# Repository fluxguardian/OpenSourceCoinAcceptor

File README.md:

# OpenSourceCoinAcceptor
 An open source coin acceptor

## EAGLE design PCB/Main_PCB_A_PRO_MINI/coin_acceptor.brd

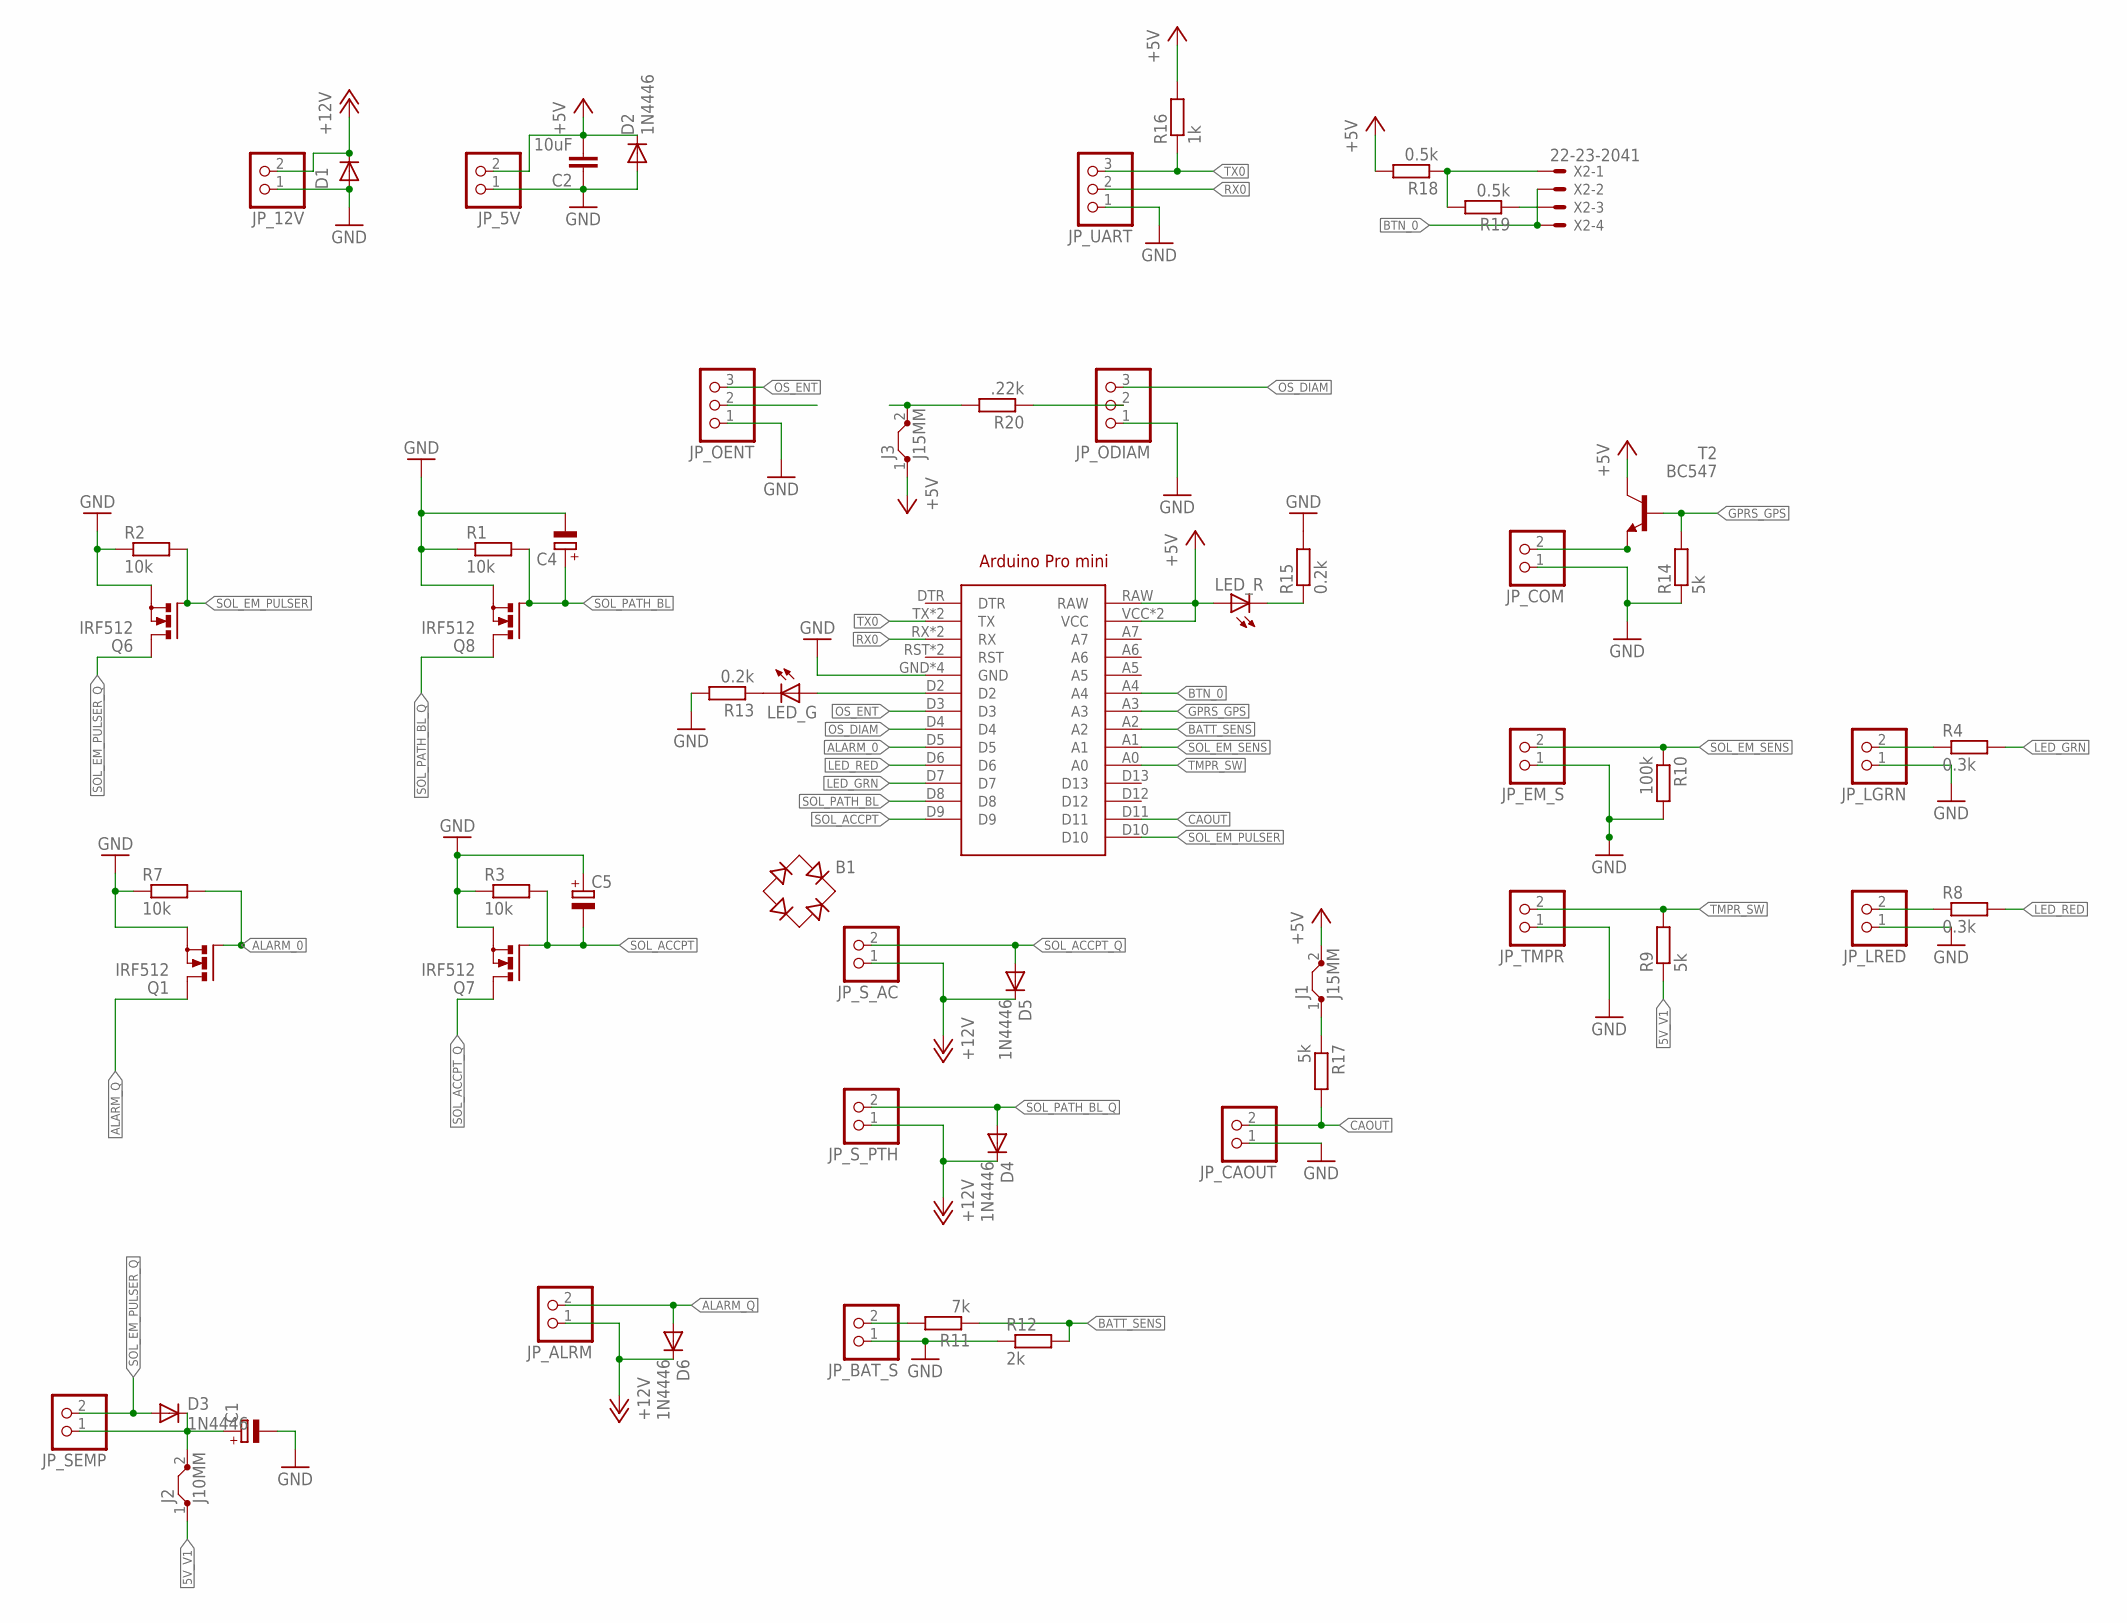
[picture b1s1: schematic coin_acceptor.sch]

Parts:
ARDUINO1: ARDUINO_PRO_MINI
B1: RB1A
C1, C4, C5: CPOL-EUE2.5-5; E2,5-5
C2: 10uF; C025-024X044
D1, D2, D3, D4, D5, D6: 1N4446; DO35-10
J1, J3: J15MM; 15
J2: J10MM; 10
JP_5V, JP_12V: PINHD-1X2; 1X02
JP_ALRM: PINHD-1X2; 1X02
JP_BAT_S: PINHD-1X2; 1X02
JP_CAOUT: PINHD-1X2; 1X02
JP_COM: PINHD-1X2; 1X02
JP_EM_S: PINHD-1X2; 1X02
JP_LGRN: PINHD-1X2; 1X02
JP_LRED: PINHD-1X2; 1X02
JP_ODIAM: PINHD-1X3; 1X03
JP_OENT: PINHD-1X3; 1X03
JP_SEMP: PINHD-1X2; 1X02
JP_S_AC: PINHD-1X2; 1X02
JP_S_PTH: PINHD-1X2; 1X02
JP_TMPR: PINHD-1X2; 1X02
JP_UART: PINHD-1X3; 1X03
LED_G: LED5MM
LED_R: LED5MM
Q1, Q6, Q7, Q8: IRF512; TO220BV
R1, R2, R3, R7: 10k; 0309/10
R4, R8: 0.3k; 0309/10
R9, R14, R17: 5k; 0309/10
R10: 100k; 0309/10
R11: 7k; 0309/10
R12: 2k; 0309/10
R13, R15: 0.2k; 0309/10
R16: 1k; 0309/10
R18, R19: 0.5k; 0309/10
R20: .22k; 0309/10
T2: BC547; TO92
X2: 22-23-2041

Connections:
5V_V0: C1.+, D3.C, J2.2, JP_SEMP.1
5V_V1: J1.1, J2.1, R9.1, R17.1
+5V: ARDUINO1.RAW, ARDUINO1.VCC, ARDUINO1.VCC@1 (VCC), C2.2, D2.C, J1.2, J3.1, JP_5V.2, LED_R.A, R16.2, R18.2, T2.3 (C)
+12V: D1.C, D4.C, D5.C, D6.C, JP_12V.2, JP_ALRM.1, JP_S_AC.1, JP_S_PTH.1
ALARM_0: ARDUINO1.D5, Q1.G, R7.2
ALARM_Q: D6.A, JP_ALRM.2, Q1.D
BATT_SENS: ARDUINO1.A2, R11.1, R12.2
BTN_0: ARDUINO1.A4, X2.2, X2.4
CAOUT: ARDUINO1.D11, JP_CAOUT.2, R17.2
COM_Q: JP_COM.2, T2.1 (E)
GND: ARDUINO1.GND, ARDUINO1.GND@1 (GND), ARDUINO1.GND@2 (GND), ARDUINO1.GND@3 (GND), C1.-, C2.1, C4.-, C5.+, D1.A, D2.A, JP_5V.1, JP_12V.1, JP_BAT_S.1, JP_CAOUT.1, JP_COM.1, JP_EM_S.1, JP_LGRN.1, JP_LRED.1, JP_ODIAM.1, JP_OENT.1, JP_TMPR.1, JP_UART.1, Q1.S, Q6.S, Q7.S, Q8.S, R1.1, R2.1, R3.1, R7.1, R10.2, R12.1, R13.2, R14.1, R15.2
GPRS_GPS: ARDUINO1.A3, R14.2, T2.2 (B)
LED_GRN: ARDUINO1.D7, R4.2
LED_RED: ARDUINO1.D6, R8.2
LGRN_Q: JP_LGRN.2, R4.1
LRED_Q: JP_LRED.2, R8.1
unnamed: JP_BAT_S.2, R11.2
unnamed: ARDUINO1.D2, LED_G.A
unnamed: LED_G.K (C), R13.1
unnamed: LED_R.K (C), R15.1
unnamed: J3.2, R20.2
unnamed: R18.1, R19.2, X2.1
unnamed: R19.1, X2.3
unnamed: JP_ODIAM.2, R20.1
OS_DIAM: ARDUINO1.D4, JP_ODIAM.3
OS_ENT: ARDUINO1.D3, JP_OENT.3
RX0: ARDUINO1.RX, ARDUINO1.RX@1 (RX), JP_UART.2
SOL_ACCPT: ARDUINO1.D9, C5.-, Q7.G, R3.2
SOL_ACCPT_Q: D5.A, JP_S_AC.2, Q7.D
SOL_EM_PULSER: ARDUINO1.D10, Q6.G, R2.2
SOL_EM_PULSER_Q: D3.A, JP_SEMP.2, Q6.D
SOL_EM_SENS: ARDUINO1.A1, JP_EM_S.2, R10.1
SOL_PATH_BL: ARDUINO1.D8, C4.+, Q8.G, R1.2
SOL_PATH_BL_Q: D4.A, JP_S_PTH.2, Q8.D
TMPR_SW: ARDUINO1.A0, JP_TMPR.2, R9.2
TX0: ARDUINO1.TX, ARDUINO1.TX@1 (TX), JP_UART.3, R16.1

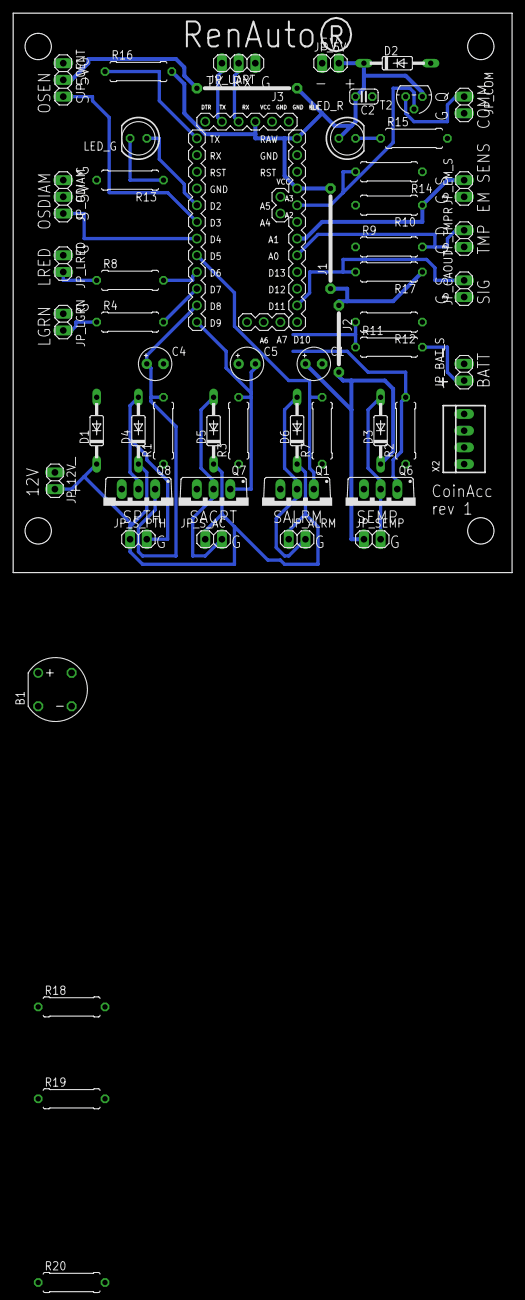
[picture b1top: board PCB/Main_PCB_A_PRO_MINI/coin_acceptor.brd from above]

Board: 2 copper layers, 75.9 x 85.1 mm, 57 parts (0 on the bottom side), 36 nets.

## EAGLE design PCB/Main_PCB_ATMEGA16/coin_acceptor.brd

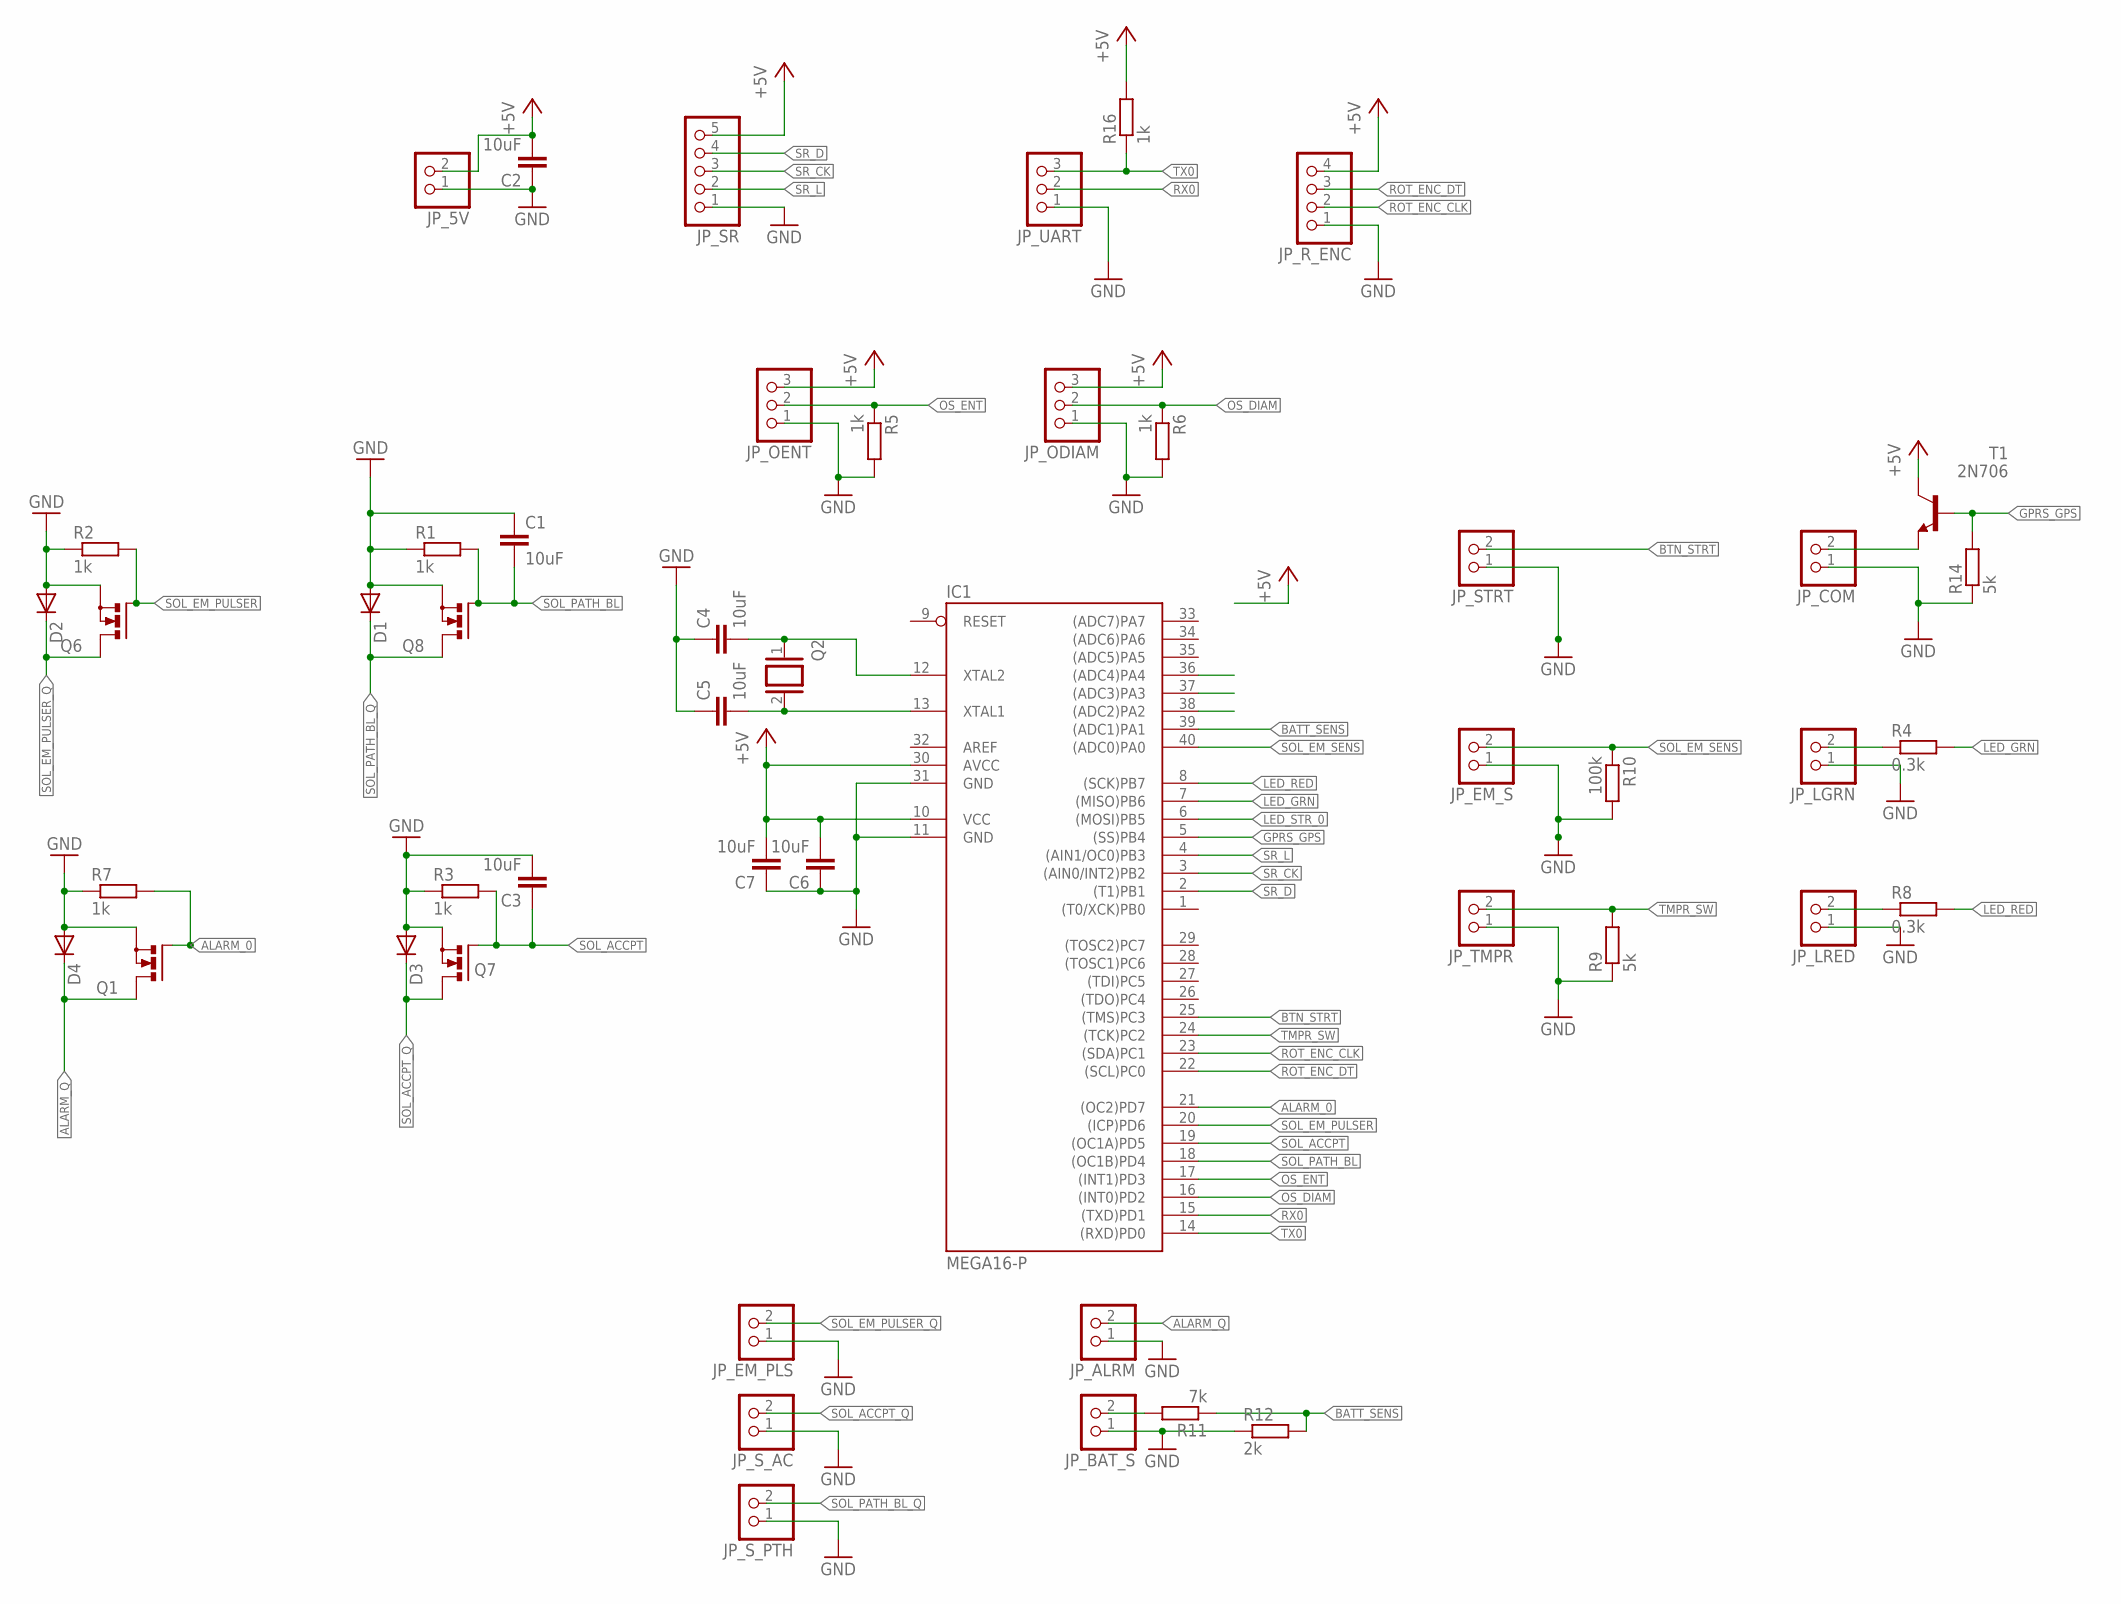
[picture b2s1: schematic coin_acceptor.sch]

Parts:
C1, C2, C3, C4, C5, C6, C7: 10uF; C025-024X044
D1, D2, D3, D4: DIODE-DO35-10; DO35-10
IC1: MEGA16-P; DIL40
JP_5V: PINHD-1X2; 1X02
JP_ALRM: PINHD-1X2; 1X02
JP_BAT_S: PINHD-1X2; 1X02
JP_COM: PINHD-1X2; 1X02
JP_EM_PLS: PINHD-1X2; 1X02
JP_EM_S: PINHD-1X2; 1X02
JP_LGRN: PINHD-1X2; 1X02
JP_LRED: PINHD-1X2; 1X02
JP_ODIAM: PINHD-1X3; 1X03
JP_OENT: PINHD-1X3; 1X03
JP_R_ENC: PINHD-1X4; 1X04
JP_SR: PINHD-1X5; 1X05
JP_STRT: PINHD-1X2; 1X02
JP_S_AC: PINHD-1X2; 1X02
JP_S_PTH: PINHD-1X2; 1X02
JP_TMPR: PINHD-1X2; 1X02
JP_UART: PINHD-1X3; 1X03
Q1, Q6, Q7, Q8: IRF512; TO220BV
Q2: XTAL; Q
R1, R2, R3, R5, R6, R7, R16: 1k; 0309/10
R4, R8: 0.3k; 0309/10
R9, R14: 5k; 0309/10
R10: 100k; 0309/10
R11: 7k; 0309/10
R12: 2k; 0309/10
T1: 2N706; TO18

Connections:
+5V: C2.2, C6.2, C7.2, IC1.10 (VCC), IC1.30 (AVCC), JP_5V.2, JP_ODIAM.3, JP_OENT.3, JP_R_ENC.4, JP_SR.5, R16.2, T1.3 (C)
ALARM_0: IC1.21 ((OC2)PD7), Q1.G, R7.2
ALARM_Q: D4.C, JP_ALRM.2, Q1.D
BATT_SENS: IC1.39 ((ADC1)PA1), R11.1, R12.2
BTN_STRT: IC1.25 ((TMS)PC3), JP_STRT.2
GND: C1.1, C2.1, C3.2, C4.1, C5.1, C6.1, C7.1, D1.A, D2.A, D3.A, D4.A, IC1.11 (GND), IC1.31 (GND), JP_5V.1, JP_ALRM.1, JP_BAT_S.1, JP_COM.1, JP_EM_PLS.1, JP_EM_S.1, JP_LGRN.1, JP_LRED.1, JP_ODIAM.1, JP_OENT.1, JP_R_ENC.1, JP_SR.1, JP_STRT.1, JP_S_AC.1, JP_S_PTH.1, JP_TMPR.1, JP_UART.1, Q1.S, Q6.S, Q7.S, Q8.S, R1.1, R2.1, R3.1, R5.2, R6.2, R7.1, R9.1, R10.2, R12.1, R14.1
GPRS_GPS: IC1.5 ((SS)PB4), R14.2, T1.2 (B)
LED_GRN: IC1.7 ((MISO)PB6), R4.2
LED_RED: IC1.8 ((SCK)PB7), R8.2
LED_STR_0: IC1.6 ((MOSI)PB5)
unnamed: JP_BAT_S.2, R11.2
unnamed: C4.2, IC1.12 (XTAL2), Q2.1
unnamed: C5.2, IC1.13 (XTAL1), Q2.2
OS_DIAM: IC1.16 ((INT0)PD2), JP_ODIAM.2, R6.1
OS_ENT: IC1.17 ((INT1)PD3), JP_OENT.2, R5.1
ROT_ENC_CLK: IC1.23 ((SDA)PC1), JP_R_ENC.2
ROT_ENC_DT: IC1.22 ((SCL)PC0), JP_R_ENC.3
RX0: IC1.15 ((TXD)PD1), JP_UART.2
SOL_ACCPT: C3.1, IC1.19 ((OC1A)PD5), Q7.G, R3.2
SOL_ACCPT_OUT2: JP_LGRN.2, R4.1
SOL_ACCPT_Q: D3.C, JP_S_AC.2, Q7.D
SOL_EM_PULSER: IC1.20 ((ICP)PD6), Q6.G, R2.2
SOL_EM_PULSER_OUT2: JP_COM.2, T1.1 (E)
SOL_EM_PULSER_Q: D2.C, JP_EM_PLS.2, Q6.D
SOL_EM_SENS: IC1.40 ((ADC0)PA0), JP_EM_S.2, R10.1
SOL_PATH_BL: C1.2, IC1.18 ((OC1B)PD4), Q8.G, R1.2
SOL_PATH_BL_OUT2: JP_LRED.2, R8.1
SOL_PATH_BL_Q: D1.C, JP_S_PTH.2, Q8.D
SR_CK: IC1.3 ((AIN0/INT2)PB2), JP_SR.3
SR_D: IC1.2 ((T1)PB1), JP_SR.4
SR_L: IC1.4 ((AIN1/OC0)PB3), JP_SR.2
TMPR_SW: IC1.24 ((TCK)PC2), JP_TMPR.2, R9.2
TX0: IC1.14 ((RXD)PD0), JP_UART.3, R16.1

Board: 2 copper layers, 49 parts (0 on the bottom side), 32 nets, no tracks yet.

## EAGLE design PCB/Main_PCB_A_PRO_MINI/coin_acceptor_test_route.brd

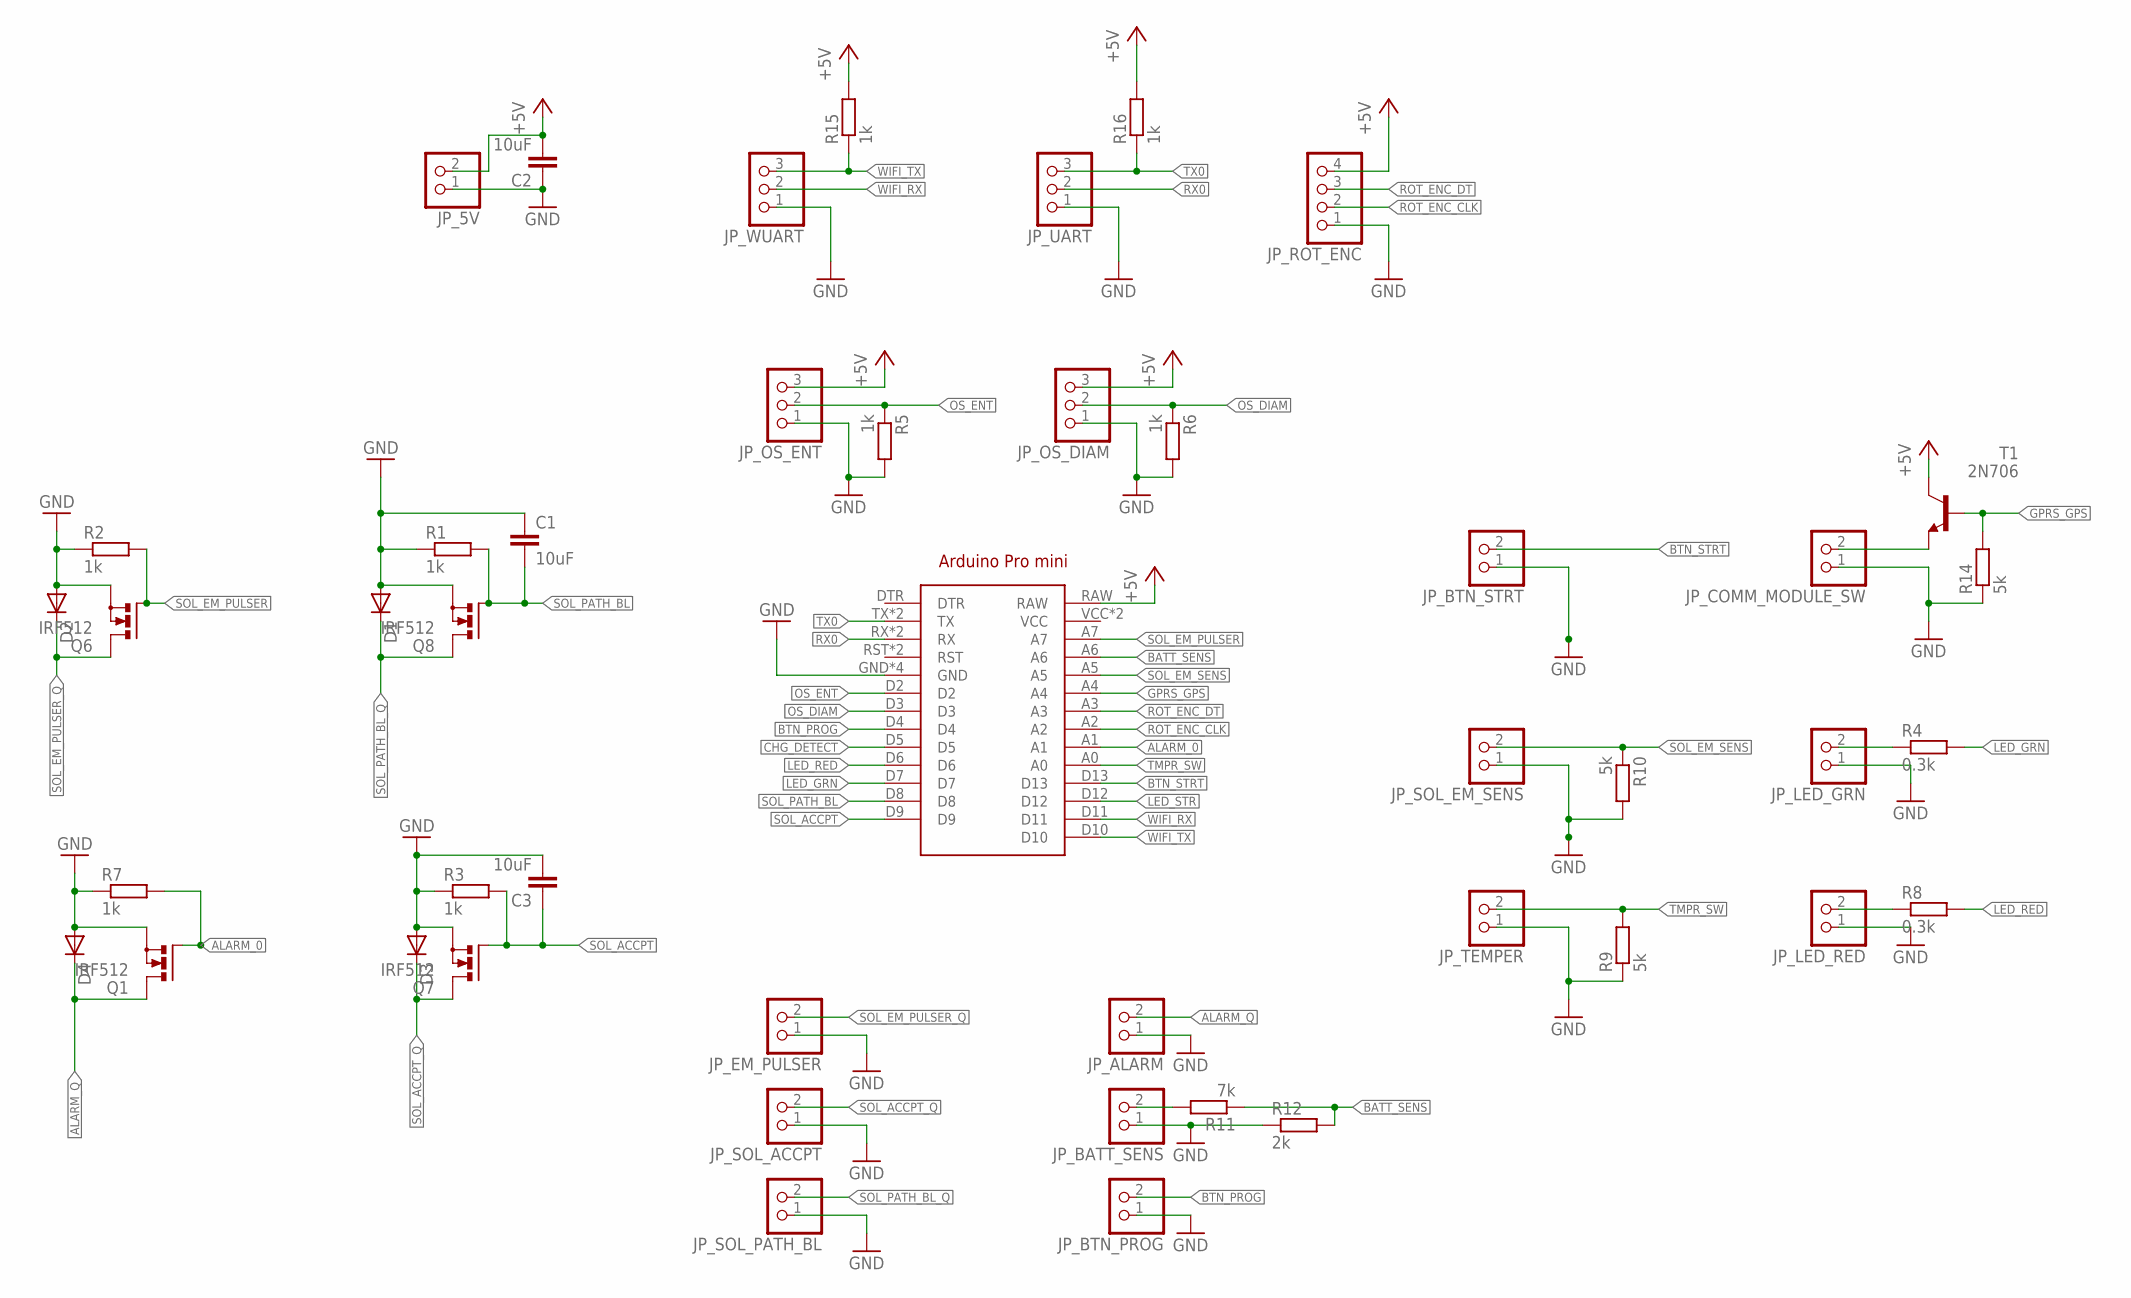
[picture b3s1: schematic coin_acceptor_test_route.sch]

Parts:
ARDUINO1: ARDUINO_PRO_MINI
C1, C2, C3: 10uF; C025-024X044
D1, D2, D3, D4: DIODE-DO35-10; DO35-10
JP_5V: PINHD-1X2; 1X02
JP_ALARM: PINHD-1X2; 1X02
JP_BATT_SENS: PINHD-1X2; 1X02
JP_BTN_PROG: PINHD-1X2; 1X02
JP_BTN_STRT: PINHD-1X2; 1X02
JP_COMM_MODULE_SW: PINHD-1X2; 1X02
JP_EM_PULSER: PINHD-1X2; 1X02
JP_LED_GRN: PINHD-1X2; 1X02
JP_LED_RED: PINHD-1X2; 1X02
JP_OS_DIAM: PINHD-1X3; 1X03
JP_OS_ENT: PINHD-1X3; 1X03
JP_ROT_ENC: PINHD-1X4; 1X04
JP_SOL_ACCPT: PINHD-1X2; 1X02
JP_SOL_EM_SENS: PINHD-1X2; 1X02
JP_SOL_PATH_BL: PINHD-1X2; 1X02
JP_TEMPER: PINHD-1X2; 1X02
JP_UART: PINHD-1X3; 1X03
JP_WUART: PINHD-1X3; 1X03
Q1, Q6, Q7, Q8: IRF512; TO220BV
R1, R2, R3, R5, R6, R7, R15, R16: 1k; 0309/10
R4, R8: 0.3k; 0309/10
R9, R10, R14: 5k; 0309/10
R11: 7k; 0309/10
R12: 2k; 0309/10
T1: 2N706; TO18

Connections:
+5V: ARDUINO1.RAW, C2.2, JP_5V.2, JP_OS_DIAM.3, JP_OS_ENT.3, JP_ROT_ENC.4, R15.2, R16.2, T1.3 (C)
ALARM_0: ARDUINO1.A1, Q1.G, R7.2
ALARM_Q: D4.C, JP_ALARM.2, Q1.D
BATT_SENS: ARDUINO1.A6, R11.1, R12.2
BTN_PROG: ARDUINO1.D4, JP_BTN_PROG.2
BTN_STRT: ARDUINO1.D13, JP_BTN_STRT.2
CHG_DETECT: ARDUINO1.D5
GND: ARDUINO1.GND, ARDUINO1.GND@1 (GND), ARDUINO1.GND@2 (GND), ARDUINO1.GND@3 (GND), C1.1, C2.1, C3.2, D1.A, D2.A, D3.A, D4.A, JP_5V.1, JP_ALARM.1, JP_BATT_SENS.1, JP_BTN_PROG.1, JP_BTN_STRT.1, JP_COMM_MODULE_SW.1, JP_EM_PULSER.1, JP_LED_GRN.1, JP_LED_RED.1, JP_OS_DIAM.1, JP_OS_ENT.1, JP_ROT_ENC.1, JP_SOL_ACCPT.1, JP_SOL_EM_SENS.1, JP_SOL_PATH_BL.1, JP_TEMPER.1, JP_UART.1, JP_WUART.1, Q1.S, Q6.S, Q7.S, Q8.S, R1.1, R2.1, R3.1, R5.2, R6.2, R7.1, R9.1, R10.2, R12.1, R14.1
GPRS_GPS: ARDUINO1.A4, R14.2, T1.2 (B)
LED_GRN: ARDUINO1.D7, R4.2
LED_RED: ARDUINO1.D6, R8.2
LED_STR: ARDUINO1.D12
unnamed: JP_BATT_SENS.2, R11.2
OS_DIAM: ARDUINO1.D3, JP_OS_DIAM.2, R6.1
OS_ENT: ARDUINO1.D2, JP_OS_ENT.2, R5.1
ROT_ENC_CLK: ARDUINO1.A2, JP_ROT_ENC.2
ROT_ENC_DT: ARDUINO1.A3, JP_ROT_ENC.3
RX0: ARDUINO1.RX, ARDUINO1.RX@1 (RX), JP_UART.2
SOL_ACCPT: ARDUINO1.D9, C3.1, Q7.G, R3.2
SOL_ACCPT_OUT2: JP_LED_GRN.2, R4.1
SOL_ACCPT_Q: D3.C, JP_SOL_ACCPT.2, Q7.D
SOL_EM_PULSER: ARDUINO1.A7, Q6.G, R2.2
SOL_EM_PULSER_OUT2: JP_COMM_MODULE_SW.2, T1.1 (E)
SOL_EM_PULSER_Q: D2.C, JP_EM_PULSER.2, Q6.D
SOL_EM_SENS: ARDUINO1.A5, JP_SOL_EM_SENS.2, R10.1
SOL_PATH_BL: ARDUINO1.D8, C1.2, Q8.G, R1.2
SOL_PATH_BL_OUT2: JP_LED_RED.2, R8.1
SOL_PATH_BL_Q: D1.C, JP_SOL_PATH_BL.2, Q8.D
TMPR_SW: ARDUINO1.A0, JP_TEMPER.2, R9.2
TX0: ARDUINO1.TX, ARDUINO1.TX@1 (TX), JP_UART.3, R16.1
VCC: ARDUINO1.VCC, ARDUINO1.VCC@1 (VCC)
WIFI_RX: ARDUINO1.D11, JP_WUART.2
WIFI_TX: ARDUINO1.D10, JP_WUART.3, R15.1

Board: 2 copper layers, 46 parts (0 on the bottom side), 31 nets, no tracks yet.

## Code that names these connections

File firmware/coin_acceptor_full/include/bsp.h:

#ifndef BSP_H
#define BSP_H
#define OPT_SENS_ENTRANCE	3
#define OPT_SENS_DIAM		4
#define ALARM_0				5
#define LED_RED_PIN			6
#define LED_GRN_PIN 		7
#define SOL_PATH_BLOCK		8
#define SOL_ACCPT_COIN		9
#define SOL_EM_PULSER		10
#define COMM_OUT			11
#define BTN_1				14 // Temper switch
#define SOL_EM_SENS			A1
#define GPS_GPRS			A3
#define BATT_SENS			A2


#define BUZZER_PIN			ALARM_0

// EEPROM ADDRESSES
#define VALID_CONTENTS_FLG			0xAB
#define ADDR_VALID_CONTENTS			0
#define COIN_DATA_OFFSET			1

#define ADDR_COIN_1_EM_AVG			1	
#define ADDR_COIN_1_BLOCK_TM_AVG	2
#define ADDR_COIN_1_EM_SD			3
#define ADDR_COIN_1_BLOCK_TM_SD		4

#define ADDR_COIN_2_EM_AVG			5
#define ADDR_COIN_2_BLOCK_TM_AVG	6
#define ADDR_COIN_2_EM_SD			7
#define ADDR_COIN_2_BLOCK_TM_SD		8

#define ADDR_COIN_3_EM_AVG			9
#define ADDR_COIN_3_BLOCK_TM_AVG	10
#define ADDR_COIN_3_EM_SD			11
#define ADDR_COIN_3_BLOCK_TM_SD		12

#define TOKEN_DATA_LEN				13
// Constants
#define EM_PULSE_PERIOD			1000
#define DELAY_EMP(x)			delayMicroseconds(x)
#define COIN_NUM				3
#define SOL_OPEN_TIME			150
#define EM_VAL_MAX				1023	// Maximm adc value on solenoid input
#define EM_MEASURE_TIME			300		// Time taken measuring em
#define READ_EM_DELAY			5		// 
#define OS_READ_DIAM_TO			2000000
#define OP_TIMEOUT				3000	// Operation timeout
#define OS_ENTRANCE_POLL_TIME	8000000	// Polling timeout for entrance optical sensor
#define OS_READ_DIAM_TIME		1500000	//
#define BTN_1_POLL_DELAY		10
#define BTN_1_HOLD_TIME_TO_PROG	10000
#define BTN_1_HOLD_TIME_TO_EJECT 1000
#define BTN_1_INTEGRAL_TO_ACTIVATE_PROG ((BTN_1_HOLD_TIME_TO_PROG/2))
#define PROG_STATE_BTN_PRESS_TO	6000	// Timeout for user to toggle button indicating the coin to be programmed in programming mode
#define UNPRSSD_BTN_STATE		HIGH	// Unpressed btn state
#define COIN_ITERATIONS_CTR		10
#define COIN_PROG_TO			15000	// Timeout if in programming mode no coins are inserted
// Machine states
#define STATE_POLL				1
#define STATE_READ_EM			2
#define STATE_READ_OS_DIAM		3
#define STATE_ACCEPT_REJECT		4
#define STATE_PROGRAMMING		5
#define STATE_CHECK_BTN_1		6
#define STATE_ABORT_EJECT		7
#define STATE_ERROR				15
// Debugging 
#define DEBUG_BAUD				9600
#define DEBUG
#ifdef DEBUG 
#define PRINT(x)				Serial.print(x)
#define PRINT_LN(x)				Serial.println(x)
#define POLL_SERIAL_INPUT()		Serial.available()
#define READ_SERIAL_INPUT()		Serial.read()
#define INIT_SERIAL(x)				Serial.begin(x)
#else
#define PRINT(x)				void
#define PRINT_LN(x)				void
#define POLL_SERIAL_INPUT()		void
#define READ_SERIAL_INPUT()		void
#endif
#endif

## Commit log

2020-04-05 Moved OpticalSensor_test/OpticalSensor.ino to tests
2020-04-06 Increased OS entrance timeout, as low timeout missed the entrance of some coins. Minor fixes in main.cpp
2020-04-06 Removed 5V direct output to optical block sensors. Removed pull-down resistors, and added .22k current protection resistors to optical sensor output.
2020-04-06 File moved
2020-04-09 Added 3D CAD models. Various
2020-04-10 Added front cover to 3D cad
2020-04-23 Bug fixes, Improvements
